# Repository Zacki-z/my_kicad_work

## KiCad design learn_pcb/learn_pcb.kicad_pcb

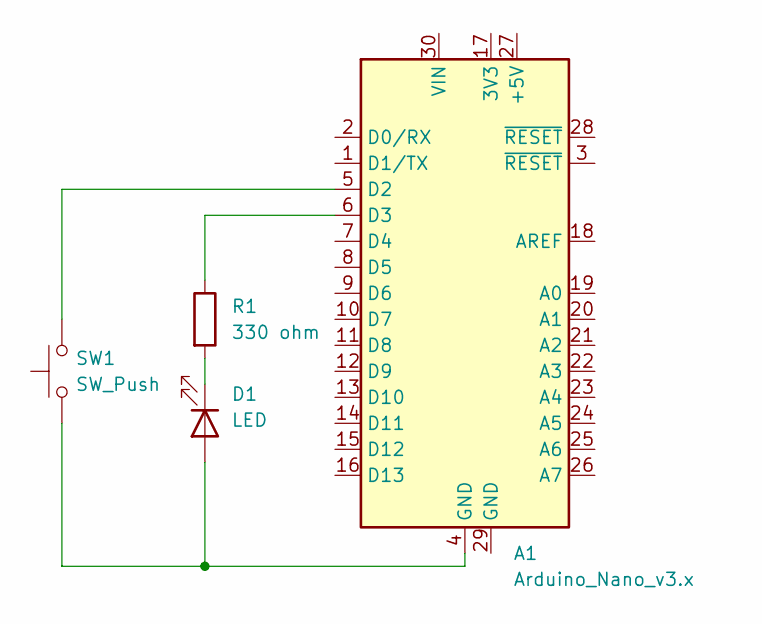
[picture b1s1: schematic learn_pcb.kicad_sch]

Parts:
A1: Arduino_Nano_v3.x; Arduino_Nano
D1: LED; LED_D3.0mm_Clear
R1: 330 ohm; R_Axial_DIN0309_L9.0mm_D3.2mm_P12.70mm_Horizontal
SW1: SW_Push; SW_PUSH_6mm_H8.5mm

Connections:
unnamed: A1.5 (D2), SW1.2
unnamed: A1.6 (D3), R1.1
unnamed: A1.4 (GND), D1.2 (A), SW1.1
unnamed: D1.1 (K), R1.2

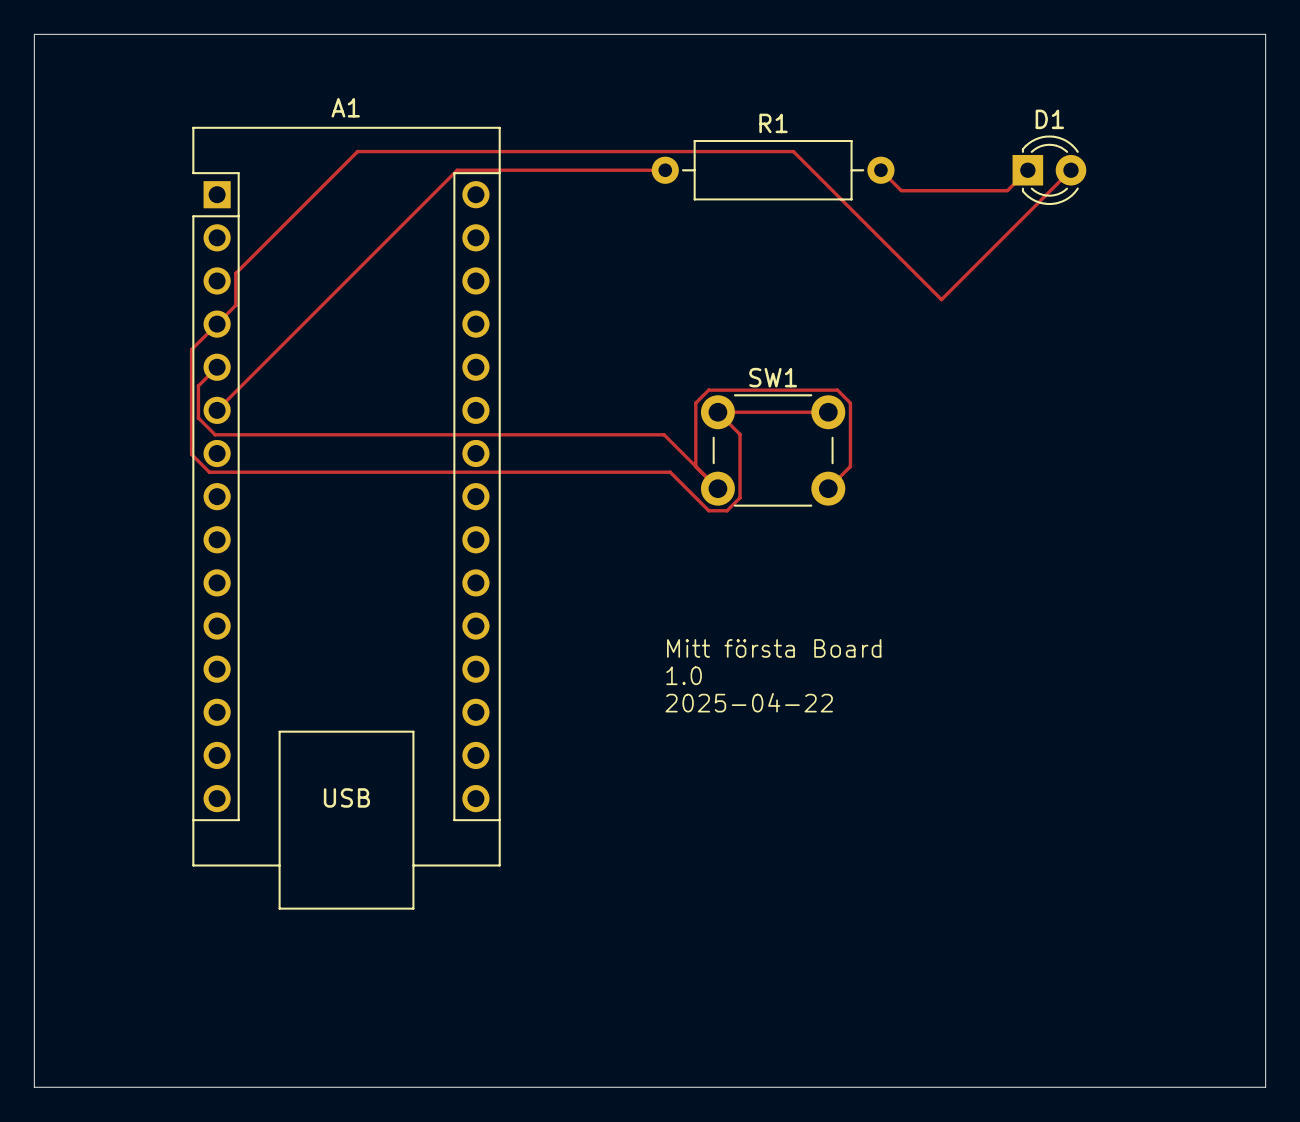
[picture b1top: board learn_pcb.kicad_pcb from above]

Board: 2 copper layers, 72.5 x 62.0 mm, 4 parts (0 on the bottom side), 4 nets.

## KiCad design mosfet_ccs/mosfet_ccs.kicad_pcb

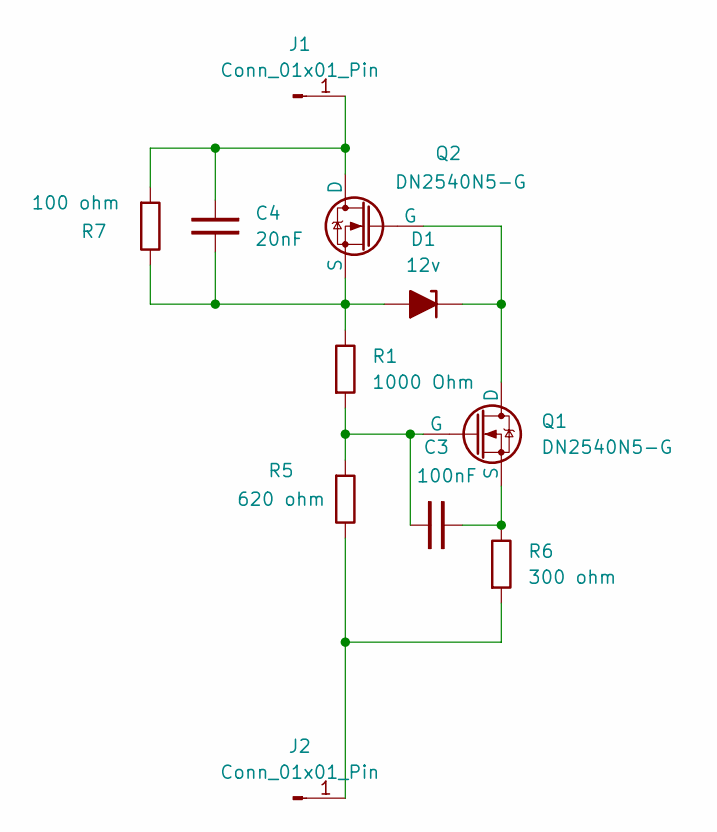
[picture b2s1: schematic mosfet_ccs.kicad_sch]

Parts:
C3: 100nF; C_Disc_D3.0mm_W2.0mm_P2.50mm
C4: 20nF; C_Disc_D3.0mm_W2.0mm_P2.50mm
D1: 12v; D_A-405_P12.70mm_Horizontal
J1, J2: Conn_01x01_Pin; TestPoint_2Pads_Pitch2.54mm_Drill0.8mm
Q1, Q2: DN2540N5-G; TO-220-3_Vertical
R1: 1000 Ohm; R_Axial_DIN0207_L6.3mm_D2.5mm_P10.16mm_Horizontal
R5: 620 ohm; R_Axial_DIN0207_L6.3mm_D2.5mm_P10.16mm_Horizontal
R6: 300 ohm; R_Axial_DIN0207_L6.3mm_D2.5mm_P10.16mm_Horizontal
R7: 100 ohm; R_Axial_DIN0207_L6.3mm_D2.5mm_P10.16mm_Horizontal

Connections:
unnamed: C4.2, D1.2 (A), Q2.3 (S), R1.2, R7.2
unnamed: D1.1 (K), Q1.2 (D), Q2.1 (G)
unnamed: C4.1, J1.1, Q2.2 (D), R7.1
unnamed: J2.1, R5.2, R6.1
unnamed: C3.1, Q1.1 (G), R1.1, R5.1
unnamed: C3.2, Q1.3 (S), R6.2

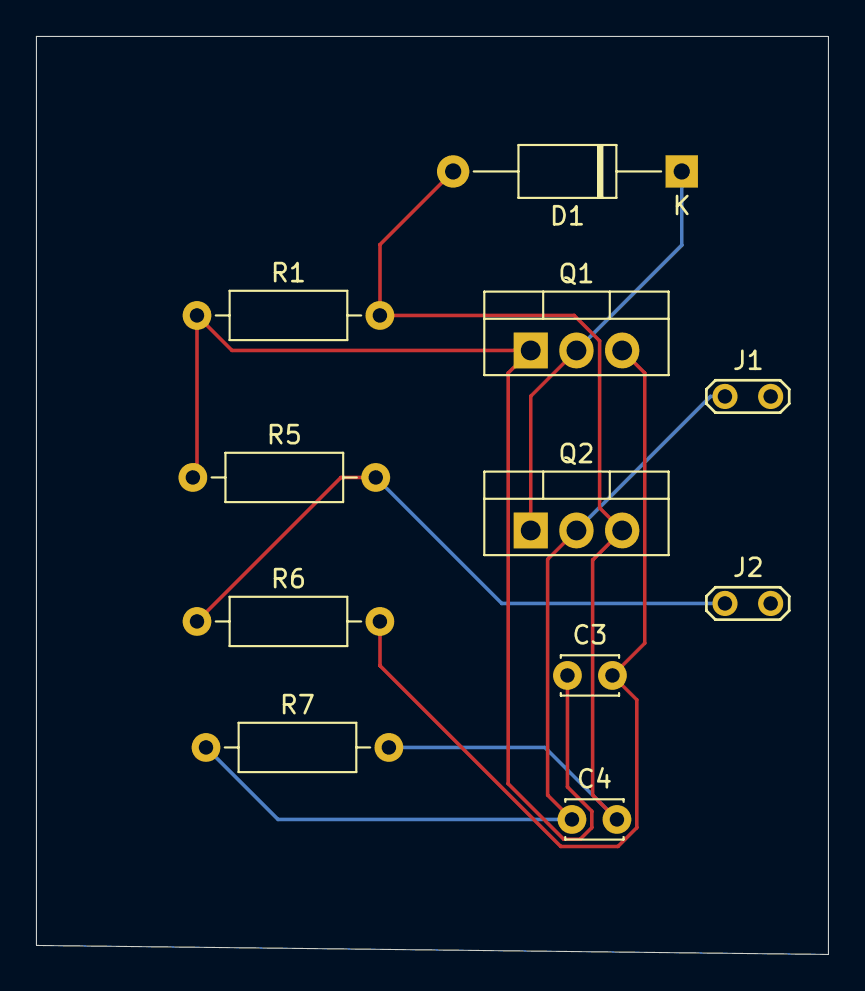
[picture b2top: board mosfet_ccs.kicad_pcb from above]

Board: 2 copper layers, 44.0 x 51.0 mm, 11 parts (0 on the bottom side), 6 nets.

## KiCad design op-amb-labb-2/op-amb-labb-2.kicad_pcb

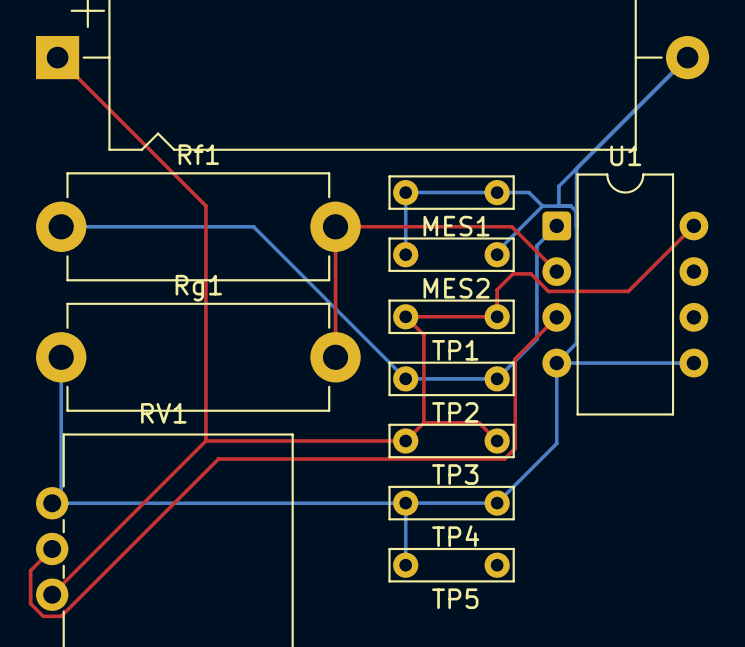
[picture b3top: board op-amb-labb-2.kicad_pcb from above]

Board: 2 copper layers, 12 parts (0 on the bottom side), 6 nets.

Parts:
C1: 100 nF; CP_Axial_L29.0mm_D10.0mm_P35.00mm_Horizontal
MES1, MES2: Voltmeter_DC; TestPoint_Bridge_Pitch5.08mm_Drill0.7mm
RV1: R_Potentiometer; Potentiometer_Vishay_148-149_Single_Vertical
Rf1: 100 kohm; R_Axial_DIN0614_L14.3mm_D5.7mm_P15.24mm_Horizontal
Rg1: 10 kohm; R_Axial_DIN0614_L14.3mm_D5.7mm_P15.24mm_Horizontal
TP1, TP2, TP3, TP4, TP5: TestPoint; TestPoint_Bridge_Pitch5.08mm_Drill0.7mm
U1: LM358; CERDIP-8_W7.62mm_SideBrazed

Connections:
unnamed: Rf1.1, TP2.1, U1.1
unnamed: C1.2, MES1.1 (-), MES2.1 (-), RV1.3, Rg1.1, TP4.1, TP5.1, U1.4 (V-), U1.5 (+)
unnamed: RV1.2, U1.3 (+)
unnamed: Rf1.2, Rg1.2, U1.2 (-)
unnamed: U1.6 (-), U1.7
unnamed: C1.1, RV1.1, TP1.1, TP3.1, U1.8 (V+)

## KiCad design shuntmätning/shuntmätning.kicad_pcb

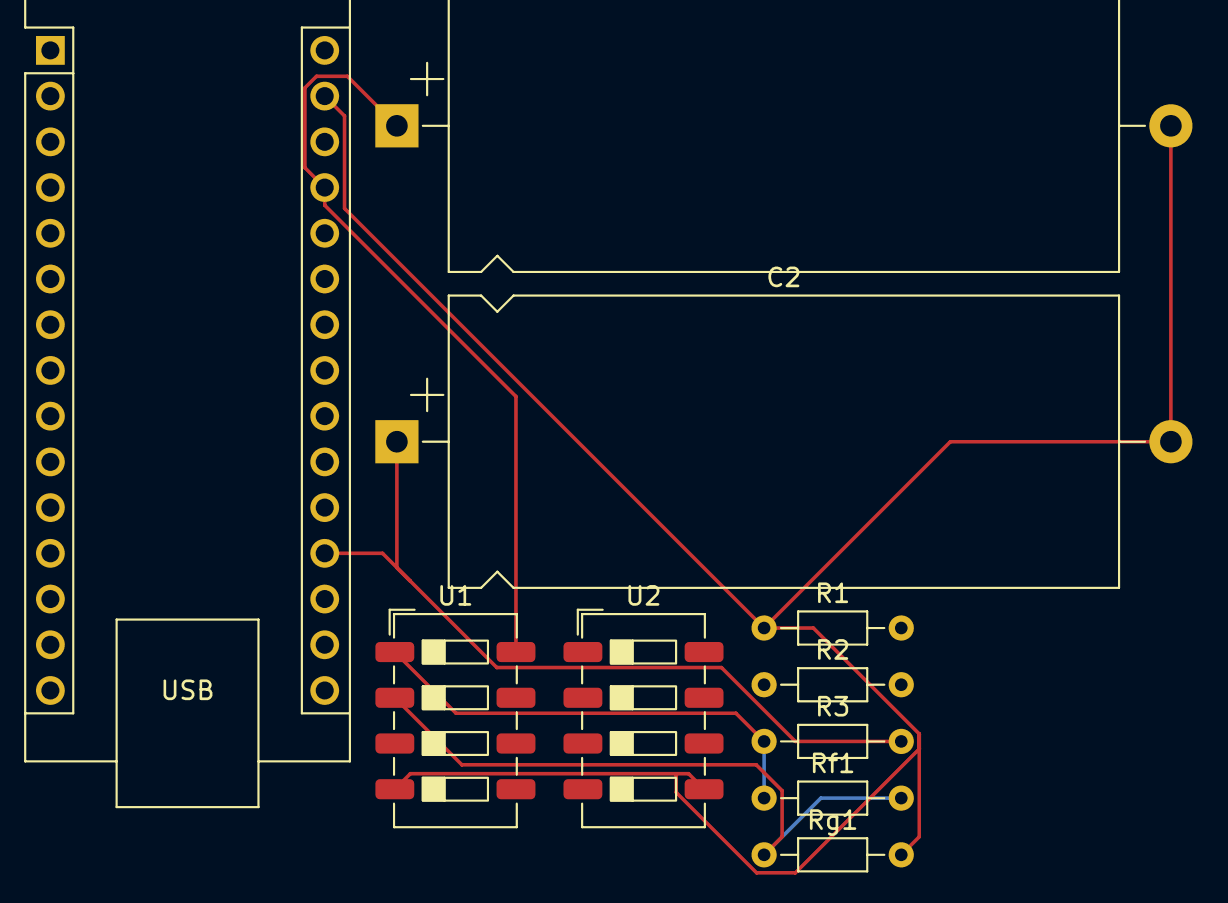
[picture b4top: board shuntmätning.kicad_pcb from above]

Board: 2 copper layers, 10 parts (0 on the bottom side), 6 nets.

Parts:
A1: Arduino_Nano_v3.x; Arduino_Nano
C1, C2: 100 nF; CP_Axial_L37.0mm_D16.0mm_P43.00mm_Horizontal
R1: 100 ohm; R_Axial_DIN0204_L3.6mm_D1.6mm_P7.62mm_Horizontal
R2: R; R_Axial_DIN0204_L3.6mm_D1.6mm_P7.62mm_Horizontal
R3: 1 kΩ; R_Axial_DIN0204_L3.6mm_D1.6mm_P7.62mm_Horizontal
Rf1: 68k Ω; R_Axial_DIN0204_L3.6mm_D1.6mm_P7.62mm_Horizontal
Rg1: 10 kΩ; R_Axial_DIN0204_L3.6mm_D1.6mm_P7.62mm_Horizontal
U1, U2: MCP6002-xP; SW_DIP_SPSTx04_Slide_6.7x11.72mm_W6.73mm_P2.54mm_LowProfile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

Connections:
Earth: A1.29 (GND), C1.2, C2.2, R1.1, Rg1.2, U1.4 (V-), U2.5 (+)
unnamed: A1.27 (+5V), C1.1, U1.8 (V+)
unnamed: A1.19 (A0), C2.1, R3.2
unnamed: R3.1, Rf1.1, U1.1
unnamed: Rf1.2, Rg1.1, U1.2 (-)
unnamed: U2.6 (-), U2.7

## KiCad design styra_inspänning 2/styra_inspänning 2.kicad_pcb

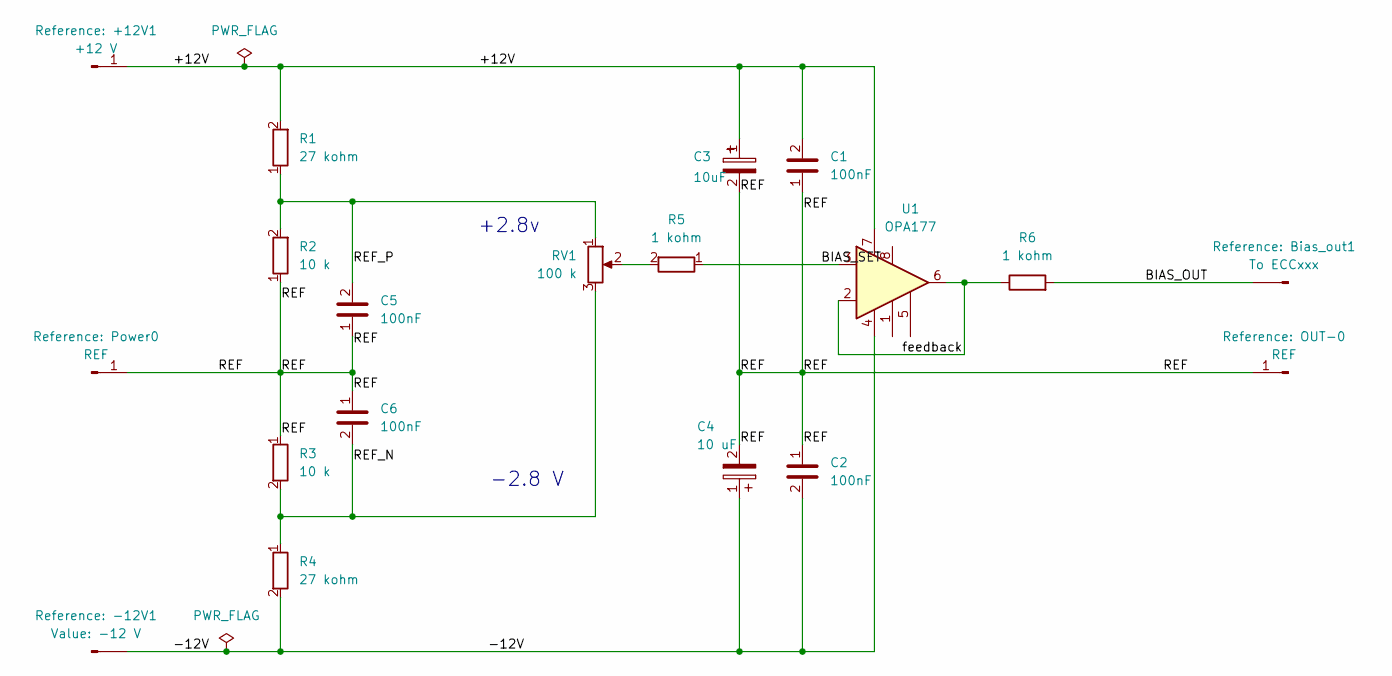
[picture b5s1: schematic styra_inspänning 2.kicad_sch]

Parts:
+12V1: +12 V; Pin_D1.0mm_L10.0mm
-12V1: -12 V; Pin_D1.0mm_L10.0mm
Bias_out1: To ECCxxx; Pin_D1.0mm_L10.0mm
C1, C2, C5, C6: 100nF; C_Disc_D3.0mm_W1.6mm_P2.50mm
C3: 10uF; CP_Radial_D5.0mm_P2.50mm
C4: 10 uF; CP_Radial_D5.0mm_P2.50mm
OUT-0: REF; Pin_D1.0mm_L10.0mm
Power0: REF; Pin_D1.0mm_L10.0mm
R1, R4: 27 kohm; R_Axial_DIN0414_L11.9mm_D4.5mm_P15.24mm_Horizontal
R2, R3: 10 k; R_Axial_DIN0414_L11.9mm_D4.5mm_P15.24mm_Horizontal
R5, R6: 1 kohm; R_Axial_DIN0414_L11.9mm_D4.5mm_P15.24mm_Horizontal
RV1: 100 k; Potentiometer_ACP_CA14-H5_Horizontal
U1: OPA177; DIP-8_W7.62mm

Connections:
/+12V: +12V1.1, C1.2, C3.1, R1.2, U1.7 (V+)
/-12V: -12V1.1, C2.2, C4.1, R4.2, U1.4 (V-)
/BIAS_OUT: Bias_out1.1, R6.2
/BIAS_SET: R5.1, U1.3 (+)
/REF: C1.1, C2.1, C3.2, C4.2, C5.1, C6.1, OUT-0.1, Power0.1, R2.1, R3.1
/REF_N: C6.2, R3.2, R4.1, RV1.3
/REF_P: C5.2, R1.1, R2.2, RV1.1
/feedback: R6.1, U1.2 (-), U1.6
unnamed: R5.2, RV1.2

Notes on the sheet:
-2.8 V
+2.8v

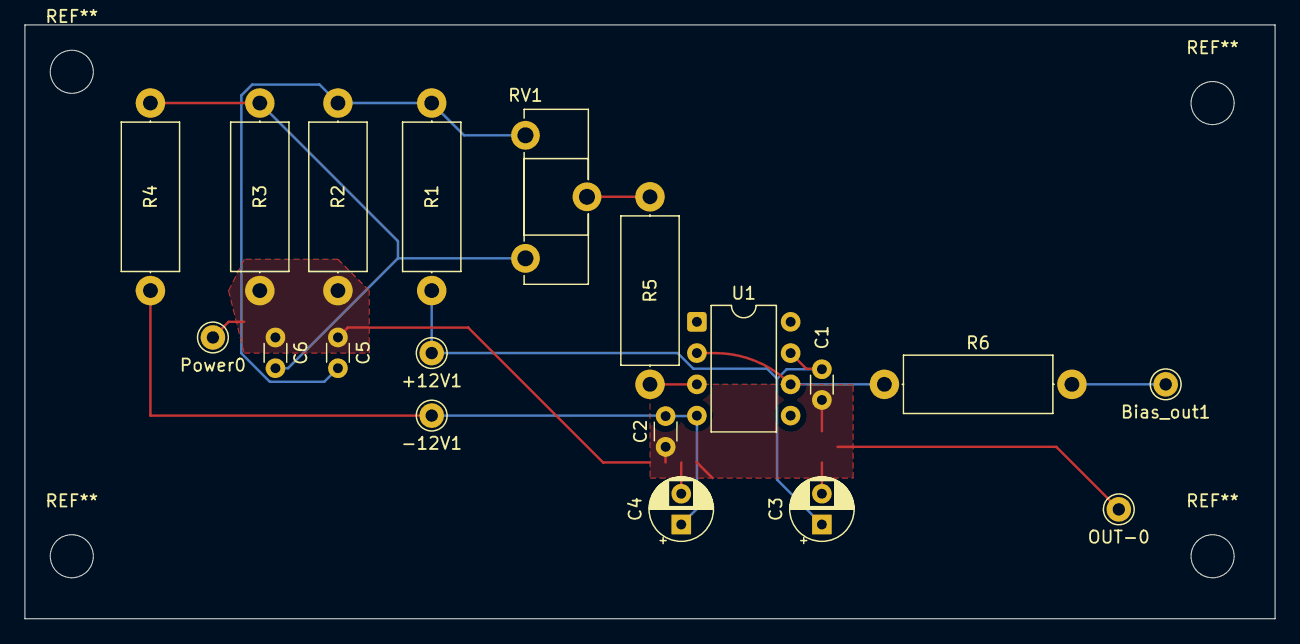
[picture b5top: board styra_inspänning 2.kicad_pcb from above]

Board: 2 copper layers, 101.6 x 48.3 mm, 19 parts (0 on the bottom side), 9 nets.

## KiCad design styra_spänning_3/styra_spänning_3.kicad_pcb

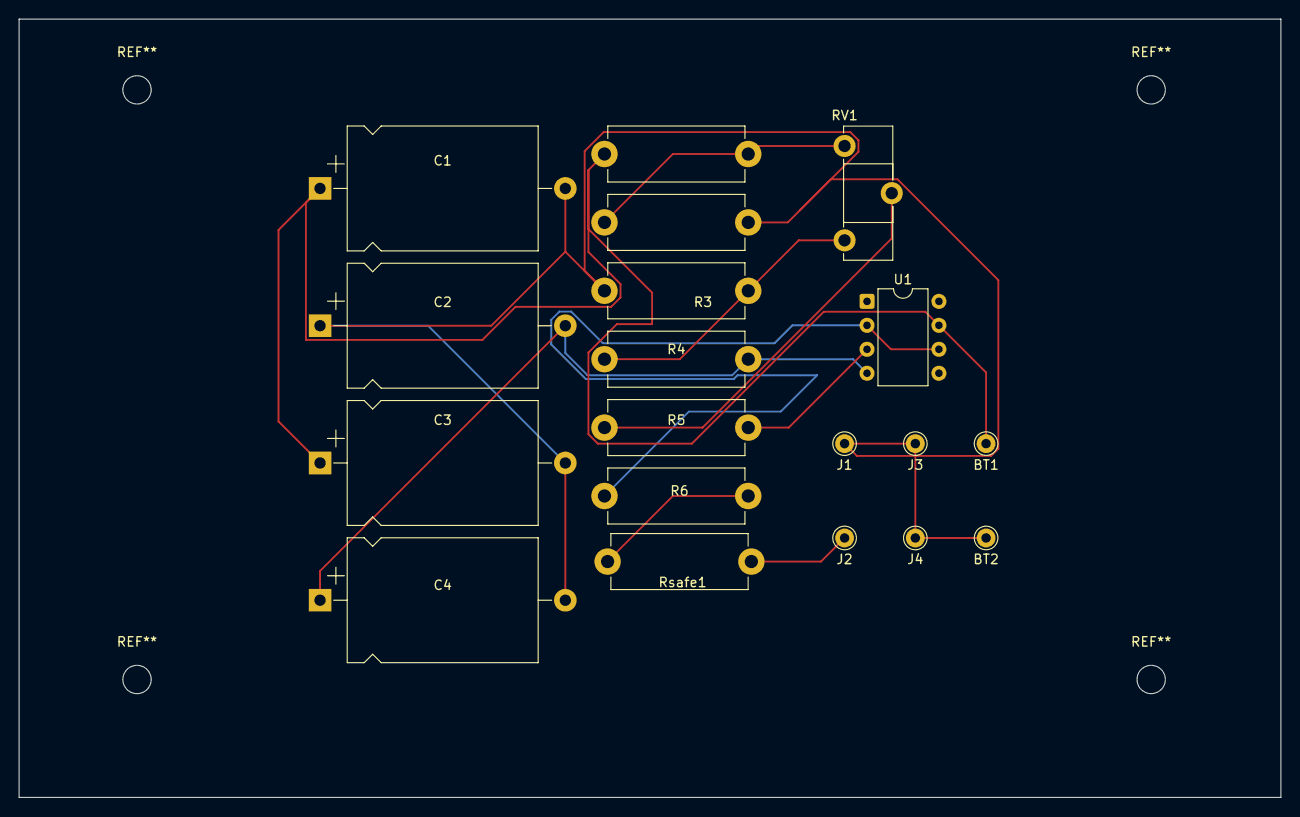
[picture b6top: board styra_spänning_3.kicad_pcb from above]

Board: 2 copper layers, 133.8 x 82.5 mm, 19 parts (0 on the bottom side), 10 nets.

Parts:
BT1, BT2: 9 v+; Pin_D1.0mm_L10.0mm
C1, C2: 100nF; CP_Axial_L20.0mm_D13.0mm_P26.00mm_Horizontal
C3: 10uF; CP_Axial_L20.0mm_D13.0mm_P26.00mm_Horizontal
C4: 10 uF; CP_Axial_L20.0mm_D13.0mm_P26.00mm_Horizontal
J1: zero return; Pin_D1.0mm_L10.0mm
J2: To ECCxxx; Pin_D1.0mm_L10.0mm
J3: BAttery 1; Pin_D1.0mm_L10.0mm
J4: BAttery 2; Pin_D1.0mm_L10.0mm
R1, R4: 47 kohm; R_Axial_DIN0614_L14.3mm_D5.7mm_P15.24mm_Horizontal
R2: 22 k; R_Axial_DIN0614_L14.3mm_D5.7mm_P15.24mm_Horizontal
R3: 22 kohm; R_Axial_DIN0614_L14.3mm_D5.7mm_P15.24mm_Horizontal
R5: 1 kohm; R_Axial_DIN0614_L14.3mm_D5.7mm_P15.24mm_Horizontal
R6: 470 ohm; R_Axial_DIN0614_L14.3mm_D5.7mm_P15.24mm_Horizontal
RV1: 10 k; Potentiometer_ACP_CA14-H5_Horizontal
Rsafe1: 470 kohm; R_Axial_DIN0614_L14.3mm_D5.7mm_P15.24mm_Horizontal
U1: OPA177; DIP-8_W7.62mm

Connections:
unnamed: BT1.1 (+), C1.1, C3.1, R1.1, U1.7 (V+)
unnamed: BT2.1 (+), C1.2, C2.1, C3.2, C4.2, J1.1, J3.1, J4.1, R2.2, R3.1
unnamed: C2.2, C4.1, R4.2, U1.4 (V-)
unnamed: J2.1, Rsafe1.2
unnamed: R1.2, R2.1, RV1.1
unnamed: R3.2, R4.1, RV1.3
unnamed: R5.1, RV1.2
unnamed: R6.2, Rsafe1.1
unnamed: R5.2, U1.3 (+)
unnamed: R6.1, U1.2 (-), U1.6
